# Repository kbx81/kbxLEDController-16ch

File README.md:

# kbx's 16-channel ESP32 Powered LED Strip Controller

## What?

Just another LED strip/tape controller...because the world needs more blinky! 💡

Note that this board is for linear/"analog" LED tape, not pixels/addressable LED tape. I recommend using a
[Quin LED](https://quinled.info) board if you need to power & drive pixels/addressable LED tape.

For more images, see the [gallery](GALLERY.md).

## Why?

I've been using more and more LED tape around my home. I wanted a replacement for/alternative to using multiple
[Magic Home](https://www.aliexpress.us/item/3256803342079819.html) LED controllers to operate multiple sections of LED
tape within a small area. Of course, having multiple controllers works, but, in my opinion, it's kind of silly and just
piles more unnecessary Wi-Fi devices onto my network. Soooooo why not make a single controller that can control a whole
bunch of strips from a single ESP32? Here we are.

In addition, I wanted something ESP32-based to minimize flicker; soft-PWM used on the ESP8266 drives me crazy in this
sense. A benefit of the ESP32 over the ESP8266 is that the ESP32 has _dedicated hardware_ for generating PWM. This
means that dimming of the LEDs is extremely smooth, consistent and flicker-free -- even at extremely low intensities!
While it's still possible on the ESP8266, LED control is just not as slick and really does not look as nice.

I've optimized this board for size (I wanted it small) and, to a lesser extent, cost. This is why it has machine-pin
headers instead of screw terminals for connecting the LED strips. I also designed it almost entirely with surface-mount
components to keep its overall footprint small -- you can easily hide it in/under a cabinet or behind/under a shelf.

While addressable LED tape is easier to drive, linear/"analog" LED tape tends to be significantly less expensive. As
fun as they are and as neat as they may look, I don't really need addressable LEDs everywhere -- linear strips work
just fine and look just as nice.

## How?

I use this board with [ESPHome](https://esphome.io) (and [Home Assistant](https://www.home-assistant.io)) but it should
work fine with [Tasmota](https://tasmota.github.io/docs/) or any other app, really.

I laid these boards out for [RGBW strips/tape](https://www.amazon.com/dp/B01D1I50UW), but they can be wired up to more
or less any kind of strips, whether monochrome, RGB, RGBW, RGBWW, the variable-color-temperature type...whatever.

They will work with a range of voltages, from 5 volts up to 24 volts.

Please see the BoM [here](kbxLEDController-16ch_bom.csv) or [here](https://octopart.com/bom-tool/OrMoA1no) for a list
of parts needed to build one. I had the PCBs fabricated by [Elecrow](https://www.elecrow.com) but nearly any PCB
fabricator should be able to manufacture these without any issues.

If you have PCBs fabricated, I _highly_ recommend having them made with 2 oz copper -- it costs a little more but
_significantly_ improves heat dissipation and allows for more current.

The schematic and PCB were drawn in [KiCad](https://www.kicad.org).

See the [ESPHome](ESPHome/) directory for a "demo" configuration you can use with [ESPHome](https://esphome.io) to test
the device after construction.

With the transistors in the BoM, _theoretically_ it should be good for up to about 60 watts per channel -- but watch
for excessive heat! Also...do not expect to be able to run all 16 channels at the full 60 watts. You're asking for
smoke and flames if you do so. Still, the layout should be pretty accommodating for high currents, especially if the
boards are fabricated with 2 oz copper (as they should be because current and heat).

## Legal stuff and License

The circuit schematics and PCB found here are licensed under the
[Creative Commons Attribution-ShareAlike 4.0 International License](http://creativecommons.org/licenses/by-sa/4.0/).

_Happy building!_

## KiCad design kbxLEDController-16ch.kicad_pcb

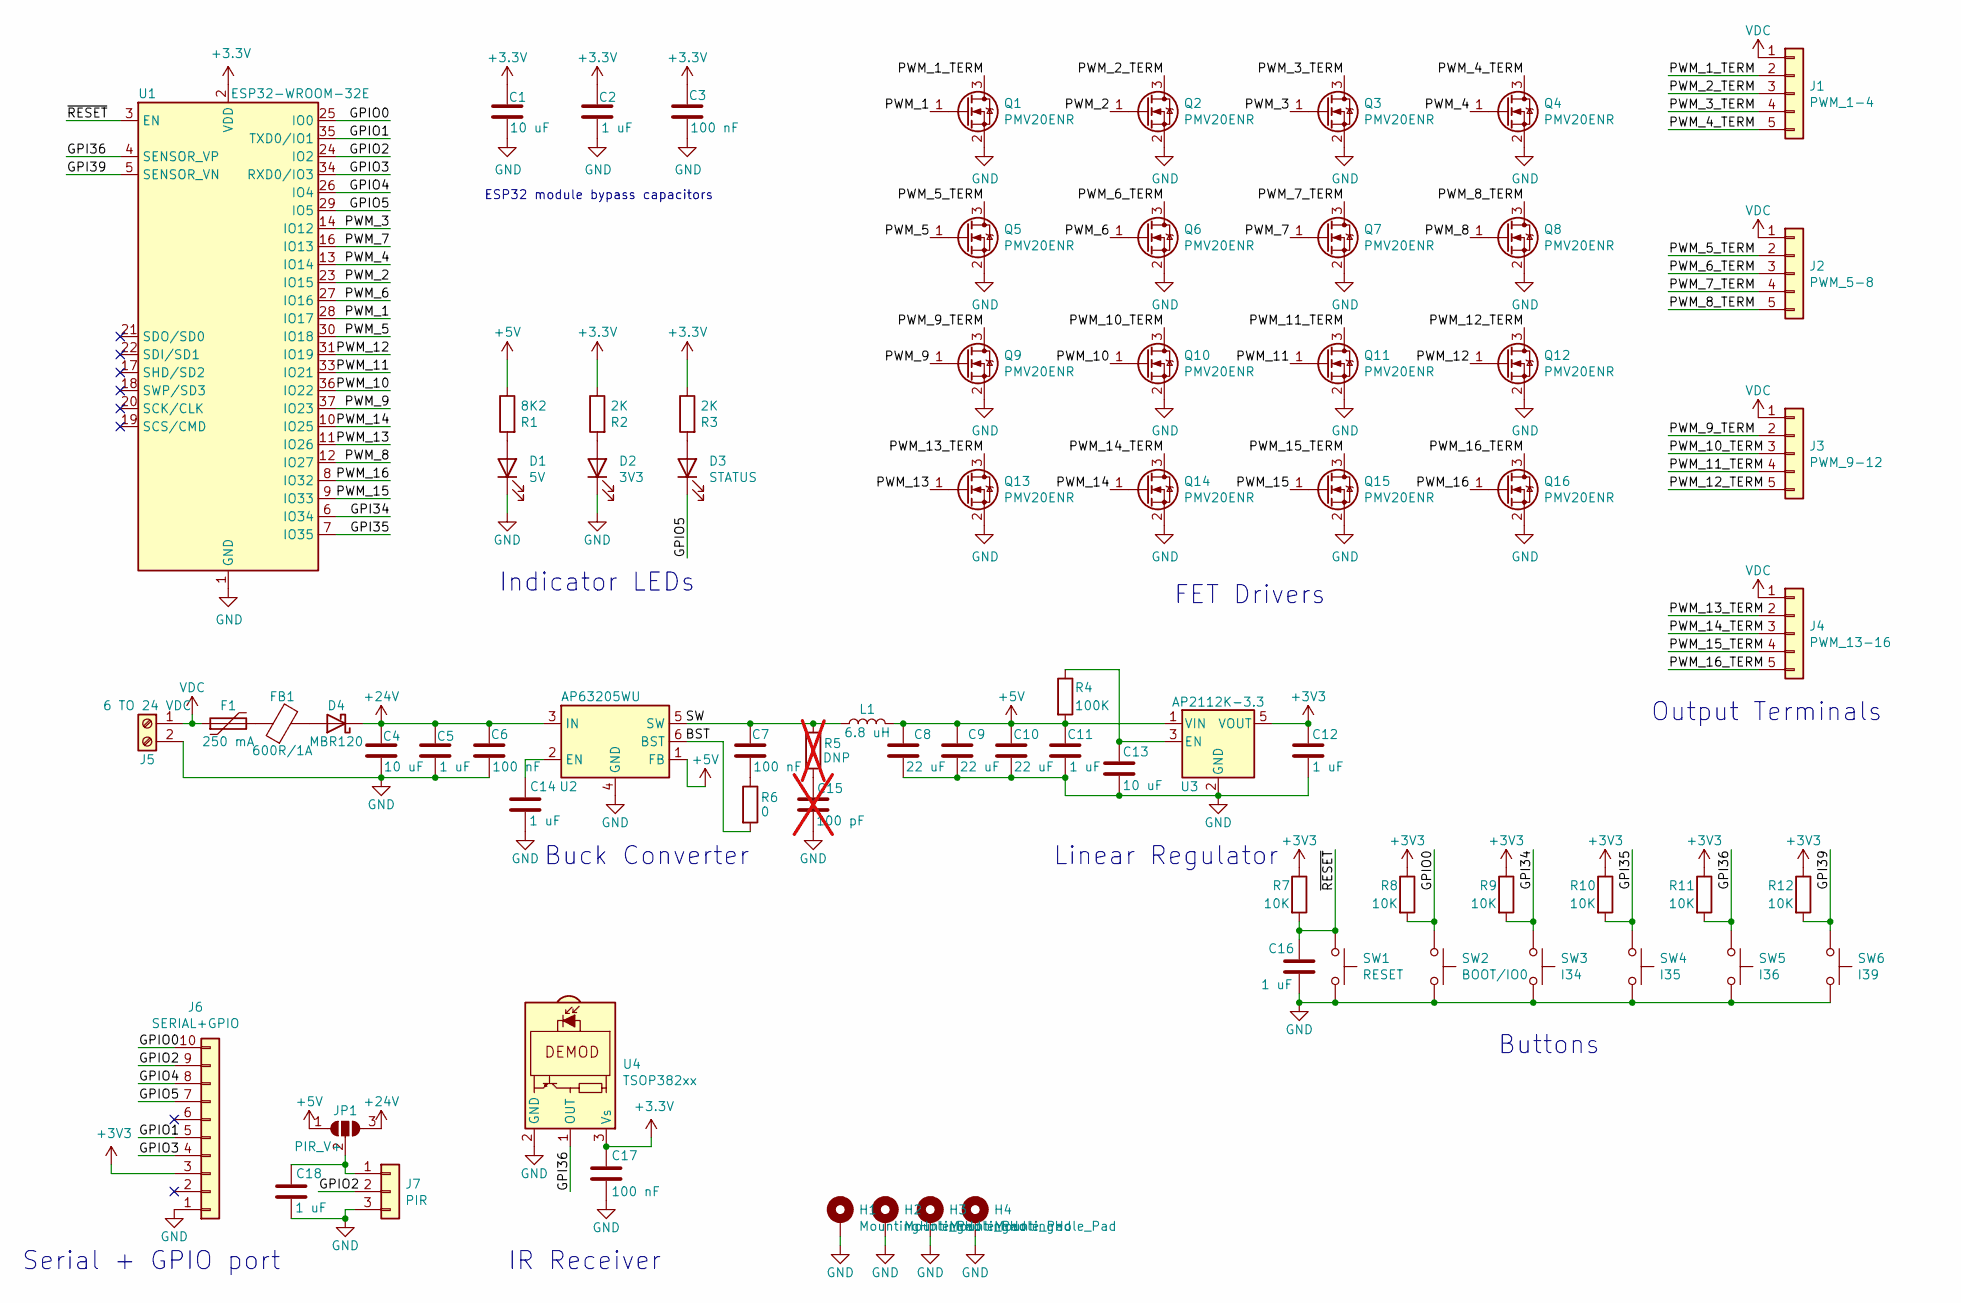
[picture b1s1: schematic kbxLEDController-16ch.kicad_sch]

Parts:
C1, C4, C13: 10 uF; C_0805_2012Metric; MPN1 C2012X5R1V106K085AC
C2, C5, C11, C12, C14, C16, C18: 1 uF; C_0805_2012Metric; MPN1 C2012X7R1H105K125AB
C3, C6, C7, C17: 100 nF; C_0805_2012Metric; MPN1 CC0805KRX7R9BB104
C8, C9, C10: 22 uF; C_0805_2012Metric; MPN1 C2012X5R1V226M125AC
C15: 100 pF; C_0805_2012Metric; MPN1 CC0805KRX7R9BB101; not fitted
D1: 5V; LED_0805_2012Metric; MPN1 LSM0805543V
D2: 3V3; LED_0805_2012Metric; MPN1 LSM0805543V
D3: STATUS; LED_0805_2012Metric; MPN1 APT2012EC
D4: MBR120; D_SOD-123; MPN1 MBR120VLSFT1G
F1: 250 mA; Fuse_1206_3216Metric; MPN1 1206L025/24YR
FB1: 600R/1A; L_0805_2012Metric; MPN1 742792031
H1, H2, H3, H4: MountingHole_Pad; MountingHole_2.2mm_M2_Pad_Via
J1: PWM_1-4; PinSocket_1x05_P2.54mm_Vertical
J2: PWM_5-8; PinSocket_1x05_P2.54mm_Vertical
J3: PWM_9-12; PinSocket_1x05_P2.54mm_Vertical
J4: PWM_13-16; PinSocket_1x05_P2.54mm_Vertical
J5: 6 TO 24 VDC; TerminalBlock_Phoenix_MKDS-1,5-2_1x02_P5.00mm_Horizontal; MPN1 1868733
J6: SERIAL+GPIO; PinSocket_1x10_P2.54mm_Vertical
J7: PIR; PinSocket_1x03_P2.54mm_Vertical
JP1: PIR_V+; SolderJumper-3_P1.3mm_Open_RoundedPad1.0x1.5mm_NumberLabels
L1: 6.8 uH; L_Murata_LQH5BPN_4.9x4.9mm; MPN1 LQH5BPN6R8M38L
Q1, Q2, Q3, Q4, Q5, Q6, Q7, Q8, Q9, Q10, Q11, Q12, Q13, Q14, Q15, Q16: PMV20ENR; SOT-23; MPN1 PMV20ENR
R1: 8K2; R_0805_2012Metric; MPN1 RC0805FR-078K2L
R2, R3: 2K; R_0805_2012Metric; MPN1 RC0805FR-072KL
R4: 100K; R_0805_2012Metric; MPN1 RC0805FR-07100KL
R5: DNP; R_0805_2012Metric; MPN1 RC0805FR-070RL; not fitted
R6: 0; R_0805_2012Metric; MPN1 RC0805FR-070RL
R7, R8, R9, R10, R11, R12: 10K; R_0805_2012Metric; MPN1 RC0805FR-0710KL
SW1: RESET; SW_Push_1P1T_NO_CK_KMR2; MPN1 KMR221GLFS
SW2: BOOT/IO0; SW_Push_1P1T_NO_CK_KMR2; MPN1 KMR221GLFS
SW3: I34; SW_Push_1P1T_NO_CK_KMR2; MPN1 KMR221GLFS
SW4: I35; SW_Push_1P1T_NO_CK_KMR2; MPN1 KMR221GLFS
SW5: I36; SW_Push_1P1T_NO_CK_KMR2; MPN1 KMR221GLFS
SW6: I39; SW_Push_1P1T_NO_CK_KMR2; MPN1 KMR221GLFS
U1: ESP32-WROOM-32E; ESP32-WROOM-32; MPN1 ESP32-WROOM-32E
U2: AP63205WU; TSOT-23-6; MPN1 AP63205WU-7
U3: AP2112K-3.3; SOT-23-5; MPN1 AP2112K-3.3TRG1
U4: TSOP382xx; Vishay_MINICAST-3Pin; MPN1 TSOP38238

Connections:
+5V: C8.2, C9.2, C10.2, C11.2, JP1.1 (A), L1.2, R1.1, R4.2, U2.1 (FB), U3.1 (VIN)
+24V: C4.2, C5.2, C6.2, D4.1 (K), JP1.3 (B), U2.3 (IN)
/BST: R6.2, U2.6 (BST)
/GPI34: R9.2, SW3.1, U1.6 (IO34)
/GPI35: R10.2, SW4.1, U1.7 (IO35)
/GPI36: R11.2, SW5.1, U1.4 (SENSOR_VP), U4.1 (OUT)
/GPI39: R12.2, SW6.1, U1.5 (SENSOR_VN)
/GPIO0: J6.10, R8.2, SW2.1, U1.25 (IO0)
/GPIO1: J6.5, U1.35 (TXD0/IO1)
/GPIO2: J6.9, J7.2, U1.24 (IO2)
/GPIO3: J6.4, U1.34 (RXD0/IO3)
/GPIO4: J6.8, U1.26 (IO4)
/GPIO5: D3.1 (K), J6.7, U1.29 (IO5)
/PWM_1: Q1.1 (G), U1.28 (IO17)
/PWM_1_TERM: J1.2, Q1.3 (D)
/PWM_2: Q2.1 (G), U1.23 (IO15)
/PWM_2_TERM: J1.3, Q2.3 (D)
/PWM_3: Q3.1 (G), U1.14 (IO12)
/PWM_3_TERM: J1.4, Q3.3 (D)
/PWM_4: Q4.1 (G), U1.13 (IO14)
/PWM_4_TERM: J1.5, Q4.3 (D)
/PWM_5: Q5.1 (G), U1.30 (IO18)
/PWM_5_TERM: J2.2, Q5.3 (D)
/PWM_6: Q6.1 (G), U1.27 (IO16)
/PWM_6_TERM: J2.3, Q6.3 (D)
/PWM_7: Q7.1 (G), U1.16 (IO13)
/PWM_7_TERM: J2.4, Q7.3 (D)
/PWM_8: Q8.1 (G), U1.12 (IO27)
/PWM_8_TERM: J2.5, Q8.3 (D)
/PWM_9: Q9.1 (G), U1.37 (IO23)
/PWM_9_TERM: J3.2, Q9.3 (D)
/PWM_10: Q10.1 (G), U1.36 (IO22)
/PWM_10_TERM: J3.3, Q10.3 (D)
/PWM_11: Q11.1 (G), U1.33 (IO21)
/PWM_11_TERM: J3.4, Q11.3 (D)
/PWM_12: Q12.1 (G), U1.31 (IO19)
/PWM_12_TERM: J3.5, Q12.3 (D)
/PWM_13: Q13.1 (G), U1.11 (IO26)
/PWM_13_TERM: J4.2, Q13.3 (D)
/PWM_14: Q14.1 (G), U1.10 (IO25)
/PWM_14_TERM: J4.3, Q14.3 (D)
/PWM_15: Q15.1 (G), U1.9 (IO33)
/PWM_15_TERM: J4.4, Q15.3 (D)
/PWM_16: Q16.1 (G), U1.8 (IO32)
/PWM_16_TERM: J4.5, Q16.3 (D)
/SW: C7.2, L1.1, R5.1, U2.5 (SW)
/~RESET: C16.1, R7.2, SW1.1, U1.3 (EN)
GND: C1.1, C2.1, C3.1, C4.1, C5.1, C6.1, C8.1, C9.1, C10.1, C11.1, C12.1, C13.1, C14.1, C15.1, C16.2, C17.2, C18.1, D1.1 (K), D2.1 (K), H1.1, H2.1, H3.1, H4.1, J5.2, J6.1, J7.3, Q1.2 (S), Q2.2 (S), Q3.2 (S), Q4.2 (S), Q5.2 (S), Q6.2 (S), Q7.2 (S), Q8.2 (S), Q9.2 (S), Q10.2 (S), Q11.2 (S), Q12.2 (S), Q13.2 (S), Q14.2 (S), Q15.2 (S), Q16.2 (S), SW1.2, SW2.2, SW3.2, SW4.2, SW5.2, SW6.2, U1.1 (GND), U1.15 (GND), U1.38 (GND), U1.39 (GND), U2.4 (GND), U3.2 (GND), U4.2 (GND)
unnamed: C7.1, R6.1
unnamed: C15.2, R5.2
unnamed: D1.2 (A), R1.2
unnamed: D2.2 (A), R2.2
unnamed: D3.2 (A), R3.2
unnamed: D4.2 (A), FB1.2
unnamed: F1.2, FB1.1
unnamed: C18.2, J7.1, JP1.2 (C)
unnamed: C14.2, U2.2 (EN)
unnamed: C13.2, R4.1, U3.3 (EN)
VDC: F1.1, J1.1, J2.1, J3.1, J4.1, J5.1

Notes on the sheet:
Linear Regulator
ESP32 module bypass capacitors
Buttons
FET Drivers
Serial + GPIO port
Output Terminals
Indicator LEDs
Buck Converter
IR Receiver

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
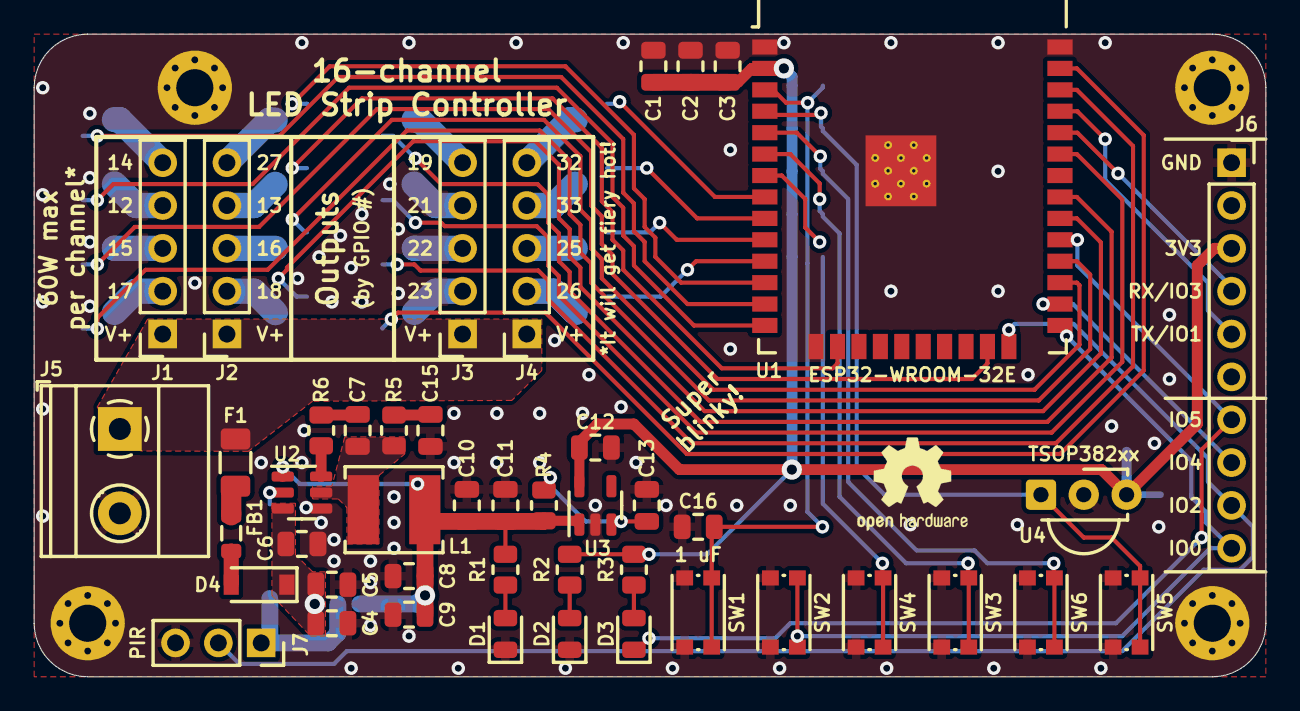
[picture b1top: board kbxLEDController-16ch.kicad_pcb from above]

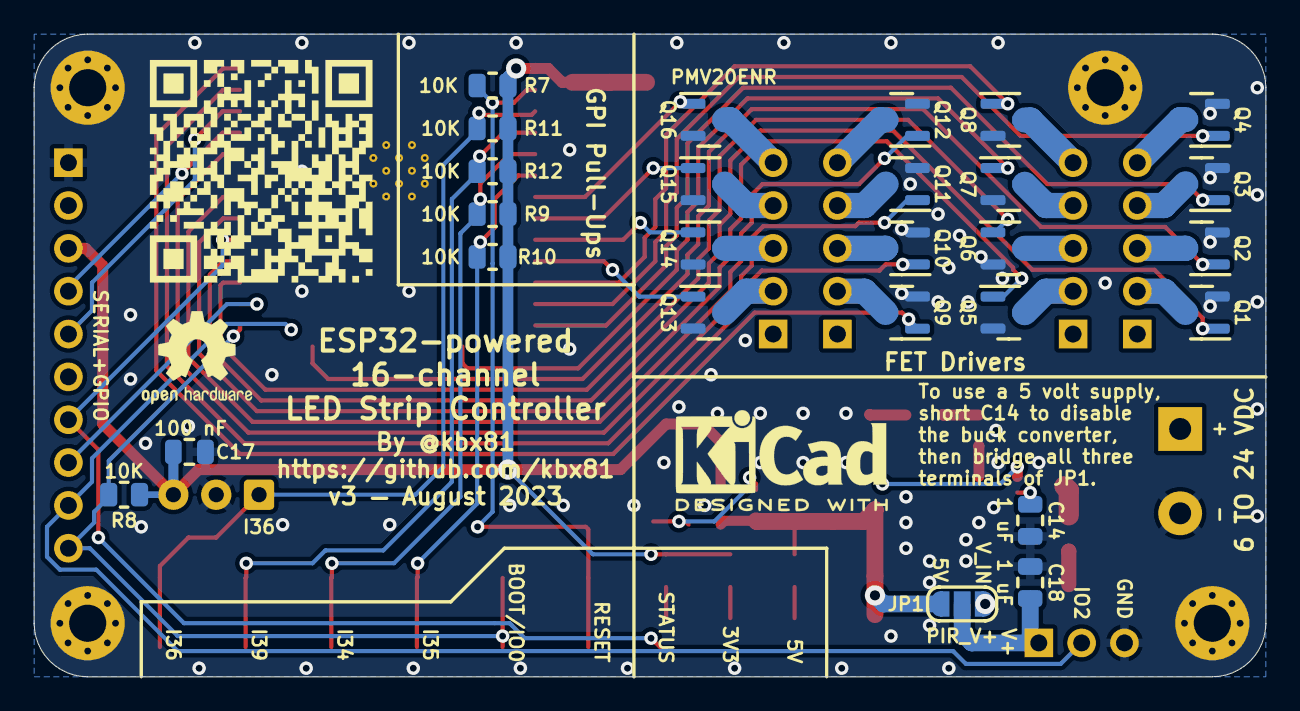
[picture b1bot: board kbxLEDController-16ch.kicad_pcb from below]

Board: 2 copper layers, 73.0 x 38.1 mm, 76 parts (27 on the bottom side), 60 nets.

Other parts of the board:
QR*****: QR

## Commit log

2023-08-27 Fix link
